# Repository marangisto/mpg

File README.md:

# mpg
Manual Pulse Generator Interface

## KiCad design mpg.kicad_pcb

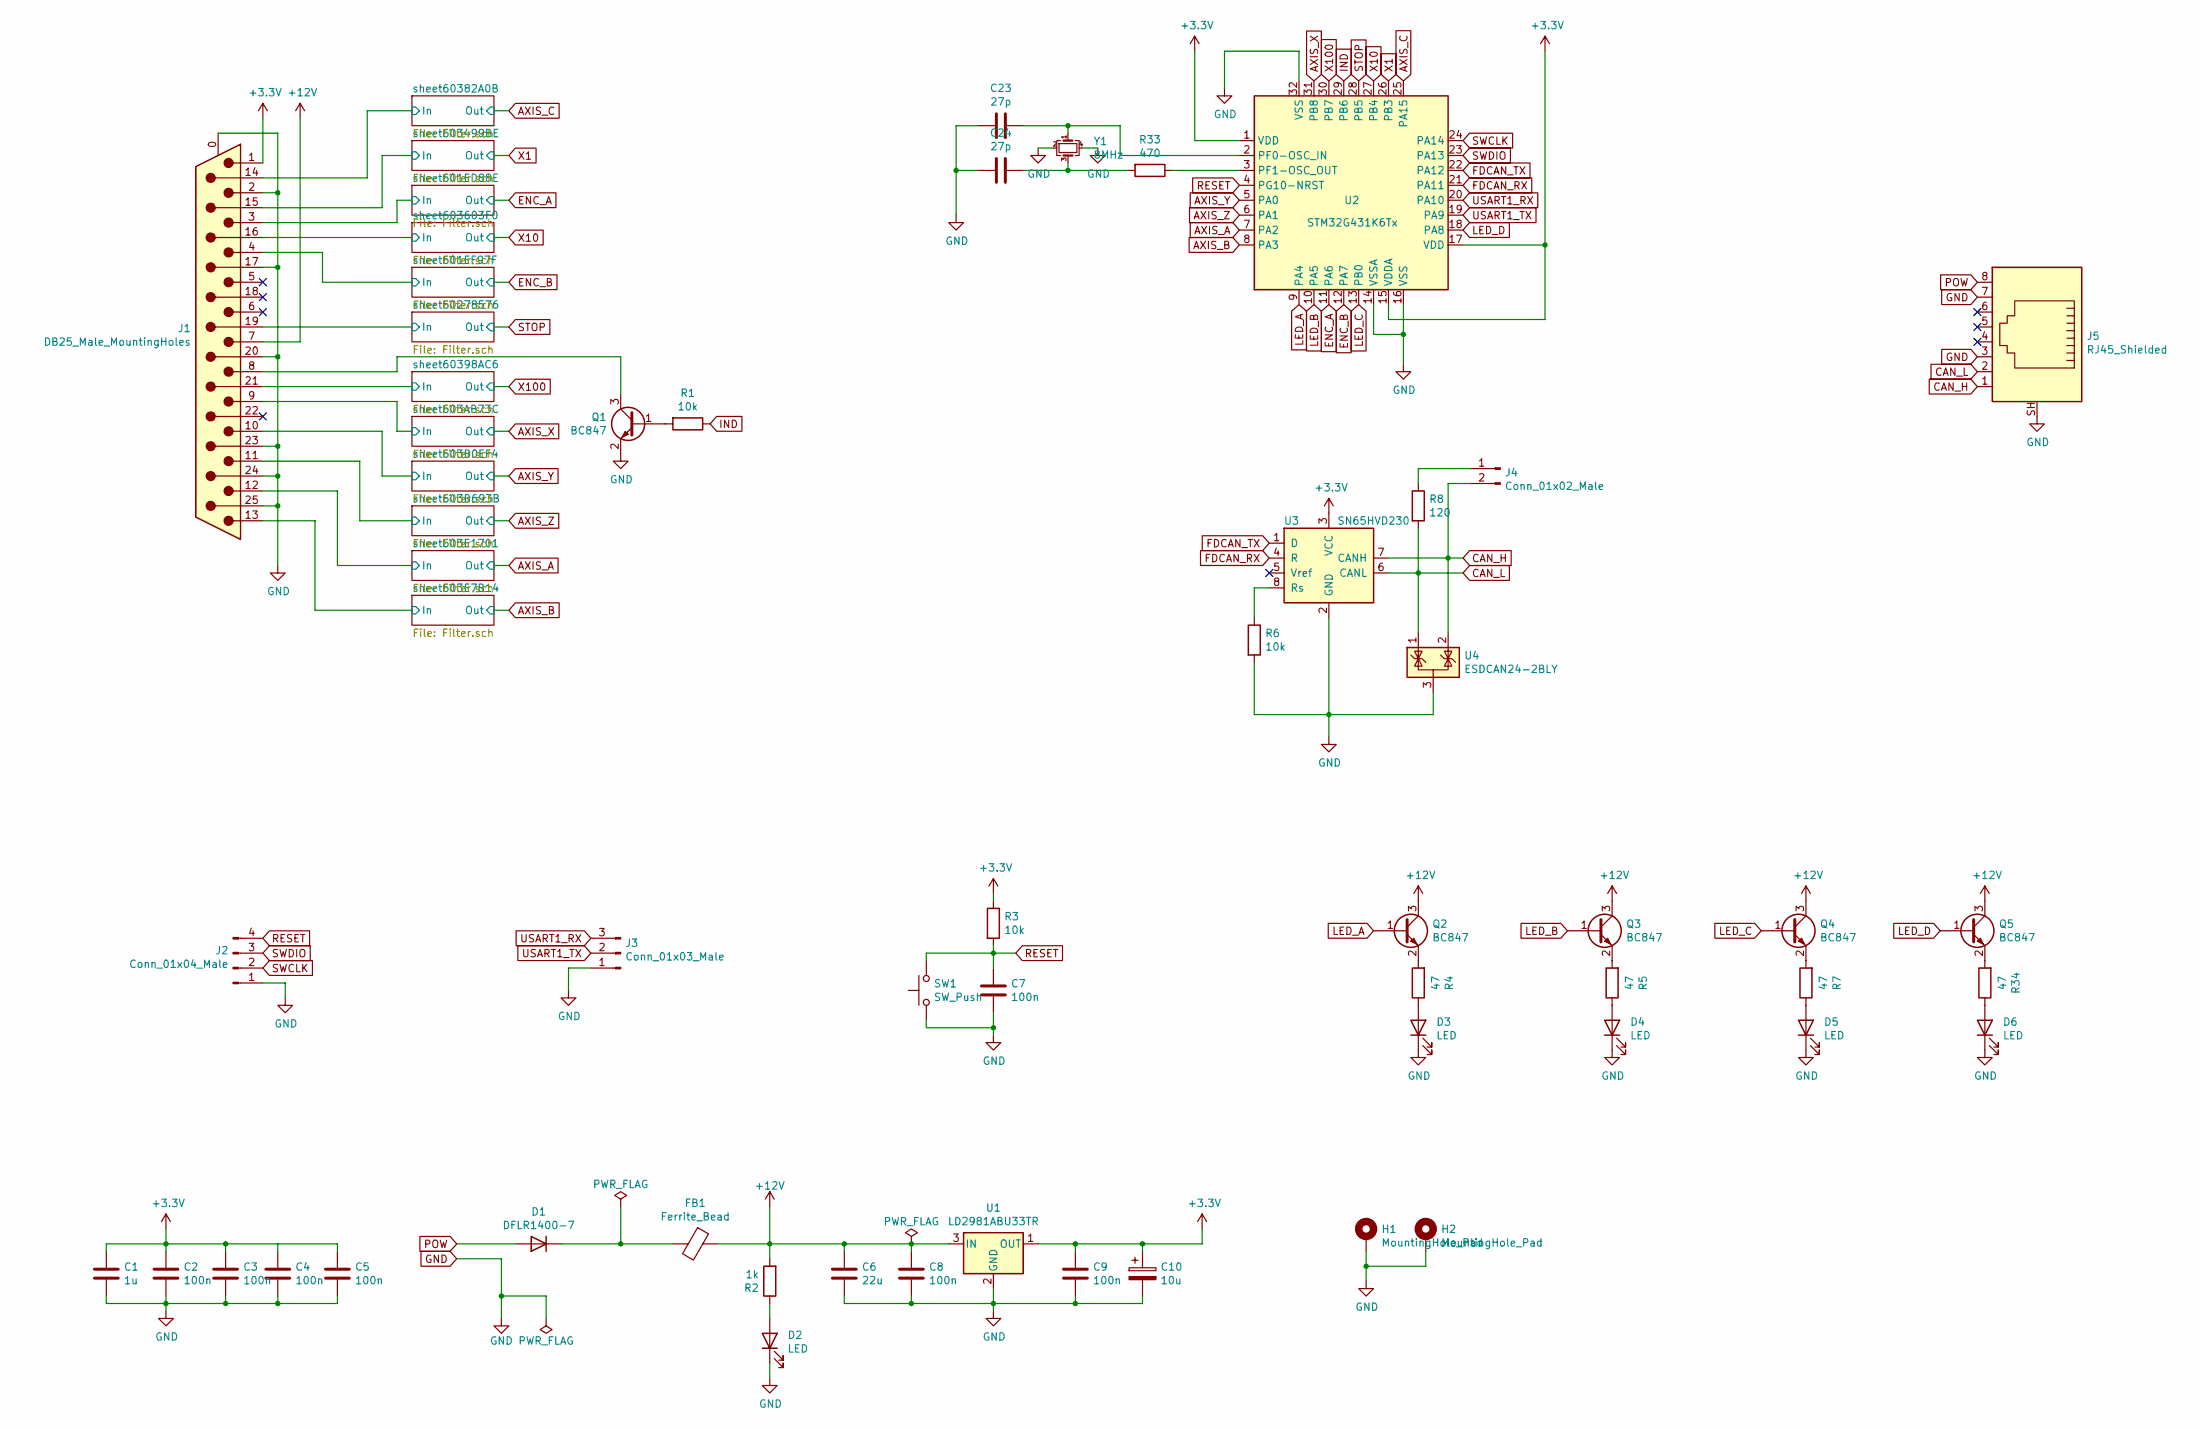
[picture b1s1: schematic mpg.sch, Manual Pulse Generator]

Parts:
C1: 1u; C_0603_1608Metric
C2, C3, C4, C5, C7, C8, C9: 100n; C_0603_1608Metric
C6: 22u; C_1206_3216Metric
C10: 10u; CP_Elec_4x5.8
C23, C24: 27p; C_0603_1608Metric
D1: DFLR1400-7; D_PowerDI-123
D2: LED; LED_0603_1608Metric_Castellated
D3, D4, D5, D6: LED; LED_D3.0mm
FB1: Ferrite_Bead; L_0603_1608Metric
H1, H2: MountingHole_Pad; MountingHole_3.2mm_M3_Pad_Via
J1: DB25_Male_MountingHoles; DSUB-25_Male_Horizontal_P2.77x2.84mm_EdgePinOffset7.70mm_Ho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
J2: Conn_01x04_Male; PinHeader_1x04_P2.54mm_Vertical
J3: Conn_01x03_Male; PinHeader_1x03_P2.54mm_Vertical
J4: Conn_01x02_Male; PinHeader_1x02_P2.54mm_Vertical
J5: RJ45_Shielded; RJ45-Wurth-615008142621
Q1, Q2, Q3, Q4, Q5: BC847; SOT-23
R1, R3, R6: 10k; R_0603_1608Metric
R2: 1k; R_0603_1608Metric
R4, R5, R7, R34: 47; R_0603_1608Metric
R8: 120; R_0603_1608Metric
R33: 470; R_0603_1608Metric
SW1: SW_Push; SW_PUSH_6mm
U1: LD2981ABU33TR; SOT-89-3
U2: STM32G431K6Tx; LQFP-32_7x7mm_P0.8mm
U3: SN65HVD230; SOIC-8_3.9x4.9mm_P1.27mm
U4: ESDCAN24-2BLY; SOT-23
Y1: 8MHz; Crystal_SMD_5032-4Pin_5.0x3.2mm

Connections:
+3V3: C1.1, C2.1, C3.1, C4.1, C5.1, C9.1, C10.1, J1.1, R3.1, U1.1 (OUT), U2.1 (VDD), U2.15 (VDDA), U2.17 (VDD), U3.3 (VCC); also elsewhere on the board
+12V: C6.1, C8.1, FB1.1, J1.7, Q2.3 (C), Q3.3 (C), Q4.3 (C), Q5.3 (C), R2.2, U1.3 (IN)
/sheet601ED88E/In: J1.3; also elsewhere on the board
/sheet601EF97F/In: J1.4; also elsewhere on the board
/sheet603AB73C/In: J1.9; also elsewhere on the board
/sheet603B0EF4/In: J1.10; also elsewhere on the board
/sheet603B693B/In: J1.11; also elsewhere on the board
/sheet603E7B14/In: J1.13; also elsewhere on the board
/sheet603E1701/In: J1.12; also elsewhere on the board
/sheet60382A0B/In: J1.14; also elsewhere on the board
/sheet60398AC6/In: J1.21; also elsewhere on the board
/sheet603499BE/In: J1.15; also elsewhere on the board
/sheet603603F0/In: J1.16; also elsewhere on the board
/sheet60278576/In: J1.19; also elsewhere on the board
AXIS_A: U2.7 (PA2); also elsewhere on the board
AXIS_B: U2.8 (PA3); also elsewhere on the board
AXIS_C: U2.25 (PA15); also elsewhere on the board
AXIS_X: U2.31 (PB8); also elsewhere on the board
AXIS_Y: U2.5 (PA0); also elsewhere on the board
AXIS_Z: U2.6 (PA1); also elsewhere on the board
CAN_H: J4.2, J5.1, U3.7 (CANH), U4.2 (K)
CAN_L: J5.2, R8.2, U3.6 (CANL), U4.1 (K)
ENC_A: U2.11 (PA6); also elsewhere on the board
ENC_B: U2.12 (PA7); also elsewhere on the board
FDCAN_RX: U2.21 (PA11), U3.4 (R)
FDCAN_TX: U2.22 (PA12), U3.1 (D)
GND: C1.2, C2.2, C3.2, C4.2, C5.2, C6.2, C7.2, C8.2, C9.2, C10.2, C23.2, C24.2, D2.1 (K), D3.1 (K), D4.1 (K), D5.1 (K), D6.1 (K), H1.1, H2.1, J1.0 (PAD), J1.2, J1.17, J1.20, J1.23, J1.24, J1.25, J2.1, J3.1, J5.3, J5.7, J5.SH, Q1.2 (E), R6.2, SW1.1, U1.2 (GND), U2.14 (VSSA), U2.16 (VSS), U2.32 (VSS), U3.2 (GND), U4.3 (A), Y1.2, Y1.4; also elsewhere on the board
IND: R1.1, U2.29 (PB6)
LED_A: Q2.1 (B), U2.9 (PA4)
LED_B: Q3.1 (B), U2.10 (PA5)
LED_C: Q4.1 (B), U2.13 (PB0)
LED_D: Q5.1 (B), U2.18 (PA8)
unnamed: C23.1, U2.2 (PF0-OSC_IN), Y1.1
unnamed: C24.1, R33.2, Y1.3
unnamed: D1.1 (K), FB1.2
unnamed: D2.2 (A), R2.1
unnamed: D3.2 (A), R4.1
unnamed: D4.2 (A), R5.1
unnamed: D5.2 (A), R7.1
unnamed: D6.2 (A), R34.1
unnamed: J1.8, Q1.3 (C)
unnamed: J4.1, R8.1
unnamed: Q1.1 (B), R1.2
unnamed: Q2.2 (E), R4.2
unnamed: Q3.2 (E), R5.2
unnamed: Q4.2 (E), R7.2
unnamed: Q5.2 (E), R34.2
unnamed: R6.1, U3.8 (Rs)
unnamed: R33.1, U2.3 (PF1-OSC_OUT)
POW: D1.2 (A), J5.8
RESET: C7.1, J2.4, R3.2, SW1.2, U2.4 (PG10-NRST)
STOP: U2.28 (PB5); also elsewhere on the board
SWCLK: J2.2, U2.24 (PA14)
SWDIO: J2.3, U2.23 (PA13)
USART1_RX: J3.3, U2.20 (PA10)
USART1_TX: J3.2, U2.19 (PA9)
X1: U2.26 (PB3); also elsewhere on the board
X10: U2.27 (PB4); also elsewhere on the board
X100: U2.30 (PB7); also elsewhere on the board

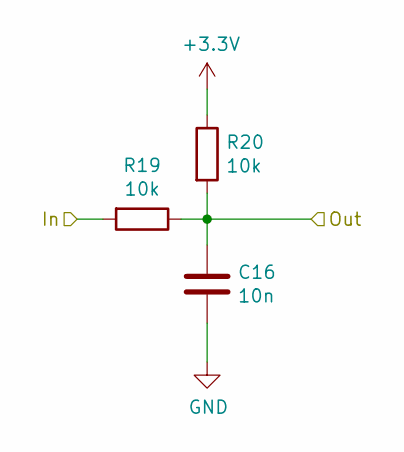
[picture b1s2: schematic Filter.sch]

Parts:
C11: 10n; C_0603_1608Metric
R9, R10: 10k; R_0603_1608Metric

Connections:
+3V3: R10.1; also elsewhere on the board
/sheet601ED88E/In: R9.2; also elsewhere on the board
ENC_A: C11.1, R9.1, R10.2; also elsewhere on the board
GND: C11.2; also elsewhere on the board

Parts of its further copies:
C12, C13, C14, C15, C16, C17, C18, C19, C20, C21, C22: 10n; C_0603_1608Metric
R11, R12, R13, R14, R15, R16, R17, R18, R19, R20, R21, R22, R23, R24, R25, R26, R27, R28, R29, R30, R31, R32: 10k; R_0603_1608Metric

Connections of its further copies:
+3V3: R12.1, R14.1, R16.1, R18.1, R20.1, R22.1, R24.1, R26.1, R28.1, R30.1, R32.1; also elsewhere on the board
/sheet601EF97F/In: R11.2; also elsewhere on the board
/sheet603AB73C/In: R23.2; also elsewhere on the board
/sheet603B0EF4/In: R25.2; also elsewhere on the board
/sheet603B693B/In: R27.2; also elsewhere on the board
/sheet603E7B14/In: R31.2; also elsewhere on the board
/sheet603E1701/In: R29.2; also elsewhere on the board
/sheet60382A0B/In: R19.2; also elsewhere on the board
/sheet60398AC6/In: R21.2; also elsewhere on the board
/sheet603499BE/In: R15.2; also elsewhere on the board
/sheet603603F0/In: R17.2; also elsewhere on the board
/sheet60278576/In: R13.2; also elsewhere on the board
AXIS_A: C21.1, R29.1, R30.2; also elsewhere on the board
AXIS_B: C22.1, R31.1, R32.2; also elsewhere on the board
AXIS_C: C16.1, R19.1, R20.2; also elsewhere on the board
AXIS_X: C18.1, R23.1, R24.2; also elsewhere on the board
AXIS_Y: C19.1, R25.1, R26.2; also elsewhere on the board
AXIS_Z: C20.1, R27.1, R28.2; also elsewhere on the board
ENC_B: C12.1, R11.1, R12.2; also elsewhere on the board
GND: C12.2, C13.2, C14.2, C15.2, C16.2, C17.2, C18.2, C19.2, C20.2, C21.2, C22.2; also elsewhere on the board
STOP: C13.1, R13.1, R14.2; also elsewhere on the board
X1: C14.1, R15.1, R16.2; also elsewhere on the board
X10: C15.1, R17.1, R18.2; also elsewhere on the board
X100: C17.1, R21.1, R22.2; also elsewhere on the board

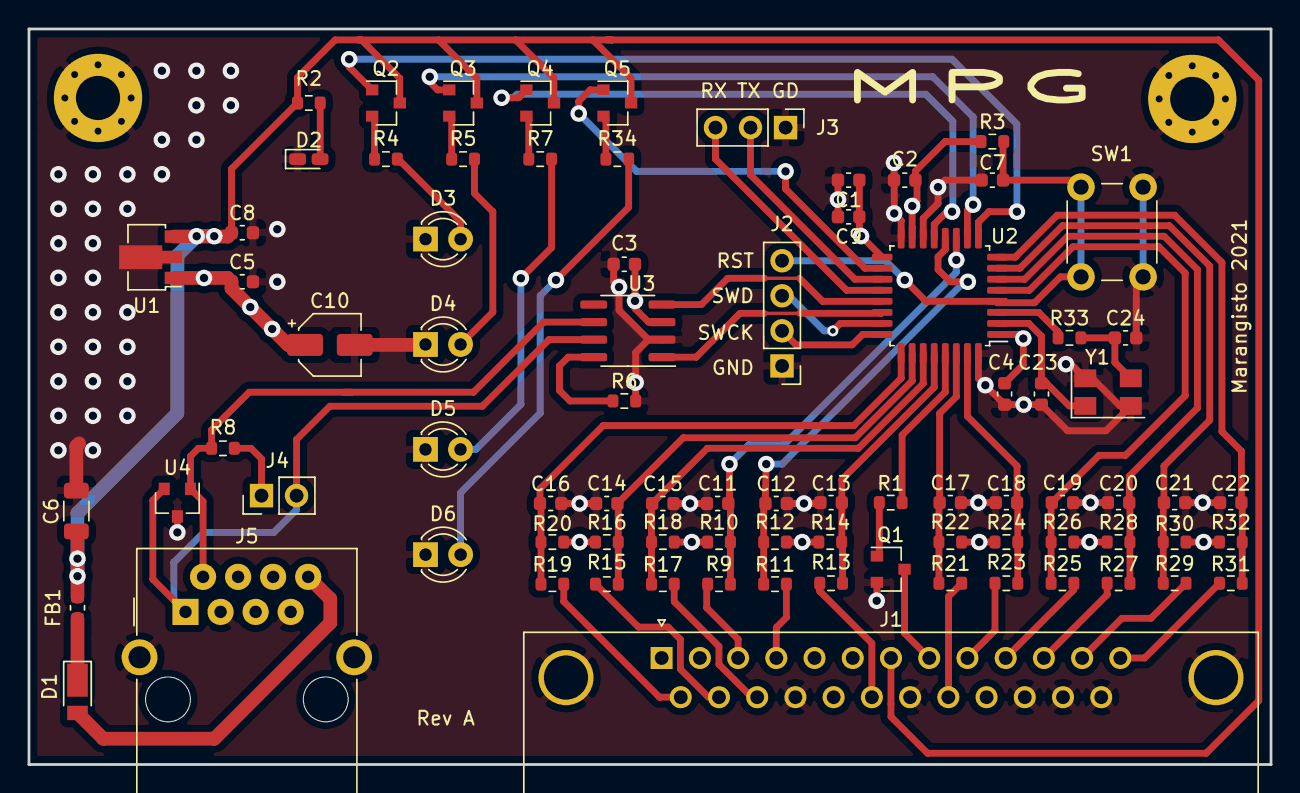
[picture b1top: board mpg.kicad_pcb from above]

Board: 4 copper layers, 90.0 x 53.3 mm, 83 parts (0 on the bottom side), 59 nets.

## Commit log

2021-01-30 Basic interfacing code for MPG.
2021-01-30 Clean-up.
2021-01-30 Use time-out to detect no axis selected.
2021-01-30 Emergency stop (no reset).
2021-01-30 Send encoder values.
2021-01-30 Added common message format.
2021-01-30 Avoid step accumulation during stop.
2021-01-30 Restructured to accumulate steps and message less often.
2021-01-30 Use indicator light for multiplier.
2021-01-30 Initial schematics design.
2021-01-31 Corrected connectors.
2021-01-31 Corrected STM32 symbol and generated PCB.
2021-01-31 Better layout.
2021-01-31 Smaller is better!
2021-02-01 Use RJ45 connector.
2021-02-03 Redesigned around G431.
2021-02-03 Minor adjustments.
2021-02-09 New RJ45 footprint and layout changes.
2021-02-09 Near final layout.
2021-02-09 Final layout.
2021-02-10 Basic routing.
2021-02-10 Completed manual track routing.
2021-02-10 Pours and soldermask.
2021-02-10 Silk-screens.
2021-02-10 Generated Gerbers.
2021-02-10 Renderings.
2021-02-10 Generated bom.
